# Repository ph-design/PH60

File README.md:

English Version | [中文版](README-zh_CN.md)

**[GitHub Repo](https://github.com/ph-design/PH60) | [Wiki](https://wiki.phdesign.cc/PH60/rev3_multi/) | [Discord](https://discord.gg/8UfQXcefPH) | [Taobao Store](https://shop268559013.taobao.com) | [QQ Group](https://qm.qq.com/q/OY0mIxSRs4) | [Customizer](https://custom.phdesign.cc)**

---

# PH60 Rev.3

**PH60 Rev.3** is a 60% tri-mode mechanical keyboard kit with an FDM 3D-printable case and the PH60 Rev.3 Multi PCB. This revision switches to the NRF52840 MCU with Bluetooth 5.3 and Nordic 2.4 GHz proprietary protocol (TBD), runs [ZMKs](https://github.com/ph-design/zmks) firmware (our fork of ZMK), and redesigns the case for wireless use and multi-layout compatibility.

## Features

### PCB

+ [Nordic NRF52840](https://www.nordicsemi.com/products/nrf52840) MCU, Bluetooth 5.3 + 2.4 GHz (TBD).
+ [ZMKs](https://github.com/ph-design/zmks) firmware with [ZMKs Studio](https://zmks.phdesign.cc/) for real-time keymap editing.
+ Multi-layout support — ANSI / ISO / WK / WKL / HHKB, plus split spacebar: 6.25u → 2.75u + 1u + 2.5u, 7u → 3u + 1u + 3u.
+ Battery powered, built-in battery connector.

> **Note on ANSI/ISO variants:** Rev.3 currently only ships the **Multi** layout PCB. The ANSI PCB in this repo is an early prototype with a fundamentally different design approach — there is no standalone ISO version. We may develop dedicated ANSI/ISO variants based on ZMKs in the future.

### Case

+ Designed for FDM 3D printing — printable on any printer with a bed ≥ 256 × 256 mm, no supports required.
+ Magnetic quick-release latches — tool-free disassembly.
+ O-ring gasket plate mount — firm, crisp feel without foam.
+ Modular battery tray and magnet drawers, fits up to 100 × 50 × 5 mm LiPo and 10 × 5 × 5 mm magnets.
+ Locking holder for wireless receivers, compatible with most commercial 2.4 GHz receiver housings.
+ Multiple outer case variants: Standard, WKL, HHKB (6u/7u), and split backspace options.

### Plates

+ Plates available for ANSI, ISO, WK, HHKB (6u/7u), LS64, EC60, and split-key variants.
+ More layouts added over time.

## What's new compared to Rev.2

| | Rev.2 | Rev.3 |
| --- | --- | --- |
| **MCU** | RP2040 | NRF52840 |
| **Connectivity** | USB only | USB + Bluetooth 5.3 + 2.4 GHz (TBD) |
| **Firmware** | QMK + VIA | ZMKs + ZMKs Studio |
| **Power** | USB powered | Battery powered |
| **Split spacebar** | Not supported | 6.25u & 7u split |
| **Case** | 3-piece modular | Magnetic quick-release, O-ring gasket |

## Customizer

Configure your PH60 Rev.3 with live 3D preview at [custom.phdesign.cc](https://custom.phdesign.cc).

---

## Project Structure

```
PH60 Rev.3
├── Assets/                         # Preview images
├── Case_Model_Rev3/                # Case 3D model files (STEP)
├── LICENSE
├── PCB_Model_Rev3/                 # PCB 3D model files
├── PCB_Rev3/
│   ├── ANSI/                       # ANSI variant (early prototype)
│   └── Multi/                      # Multi-layout variant (primary)
├── Plates_Rev3/                    # Plate files (STEP)
├── Production/
│   ├── PH60-Rev3-ANSI/             # ANSI production files
│   └── PH60-Rev3-Multi/            # Multi production files
├── README.md
└── README-zh_CN.md
```

## Printing Guide

The case prints well with default FDM settings. Recommended parameters for best results:

| Setting | Recommended | Notes |
| --- | --- | --- |
| Filament | PLA or PETG | High-temp materials increase warp risk |
| Layer height | 0.2 mm | Model designed around 0.2 mm |
| Wall count | 2 walls | — |
| Infill pattern | Gyroid | — |
| Infill density | 15% | — |
| Wall generator | Arachne | Improves print speed |
| Accurate outer wall | Enabled | Reduces visible layer lines |
| Support | Off | Designed for supportless printing |

Make sure the bed is leveled and clean before printing. Use adhesive on long parts like the top cover to prevent warping. Sand and clean prints for a better finish.

## Assembly

### Bill of Materials

| Item | Qty | Notes |
| --- | --- | --- |
| 3D printed case parts | 1 set | PLA or PETG recommended |
| PH60 Rev.3 Multi PCB | 1 | Pre-soldered SMD components |
| MX-compatible switches | 61+ | Varies by layout |
| Keycaps | 1 set | Compatible with 60% layout |
| LiPo battery (optional) | 1 | Recommended: 100 × 50 × 5 mm, Molex 1.25 mm connector |
| Magnets | 8 | Recommended: 10 × 5 × 3 mm, N52 |
| Silicone O-rings | 8 | OD 9 mm, cord 1.5 mm |
| Silicone anti-slip pads | 4 | Recommended: 20 × 10 × 2 mm |

For detailed assembly steps, refer to the [Wiki](https://wiki.phdesign.cc/PH60/rev3_multi/).

## Firmware

### Getting Firmware

- **GitHub Actions**: Download from the [ZMKs config repository](https://github.com/ph-design/ph_lite-zmk-config) Actions artifacts.
- **QQ Group**: Join [512933670](https://qm.qq.com/q/OY0mIxSRs4) for firmware files in group shared folder.

### Flashing Firmware

1. **Enter bootloader**: Press `FN + B + R`, or remove the spacebar keycap and double-tap the `BOOT` pads with tweezers.
2. **Flash**: The keyboard appears as a USB storage device. Copy the `.uf2` file to it — the keyboard reboots automatically.

### Keymap Customization

Visit [ZMKs Studio](https://zmks.phdesign.cc/) for real-time keymap editing.

## FAQ

**Q: Which 3D printers can print the Rev.3 case?**
A: Any FDM printer with a bed ≥ 256 × 256 mm that can print PLA or PETG.

**Q: Which layouts does the Rev.3 case support?**
A: ANSI, ISO, HHKB, WK, WKL, LS64, and EC60 (NIZ electrostatic capacitive). Plate designs are continuously updated.

**Q: Why is there no dedicated ANSI or ISO PCB?**
A: The early ANSI prototype has a fundamentally different design from the Multi PCB. We focused on Multi to support all layouts with a single board. Dedicated variants may come later based on ZMKs.

**Q: What battery and magnet sizes are supported?**
A: Up to 100 × 50 × 5 mm LiPo battery. Magnets: 10 × 5 × 3 mm (N52 recommended). The battery tray and magnet drawers can be modified for other sizes.

## Getting Help

- GitHub Issues: [ph-design/PH60](https://github.com/ph-design/PH60/issues)
- Discord: [discord.gg/phdesign](https://discord.gg/8UfQXcefPH)
- QQ Group: [512933670](https://qm.qq.com/q/OY0mIxSRs4)
- Wiki: [wiki.phdesign.cc](https://wiki.phdesign.cc/)

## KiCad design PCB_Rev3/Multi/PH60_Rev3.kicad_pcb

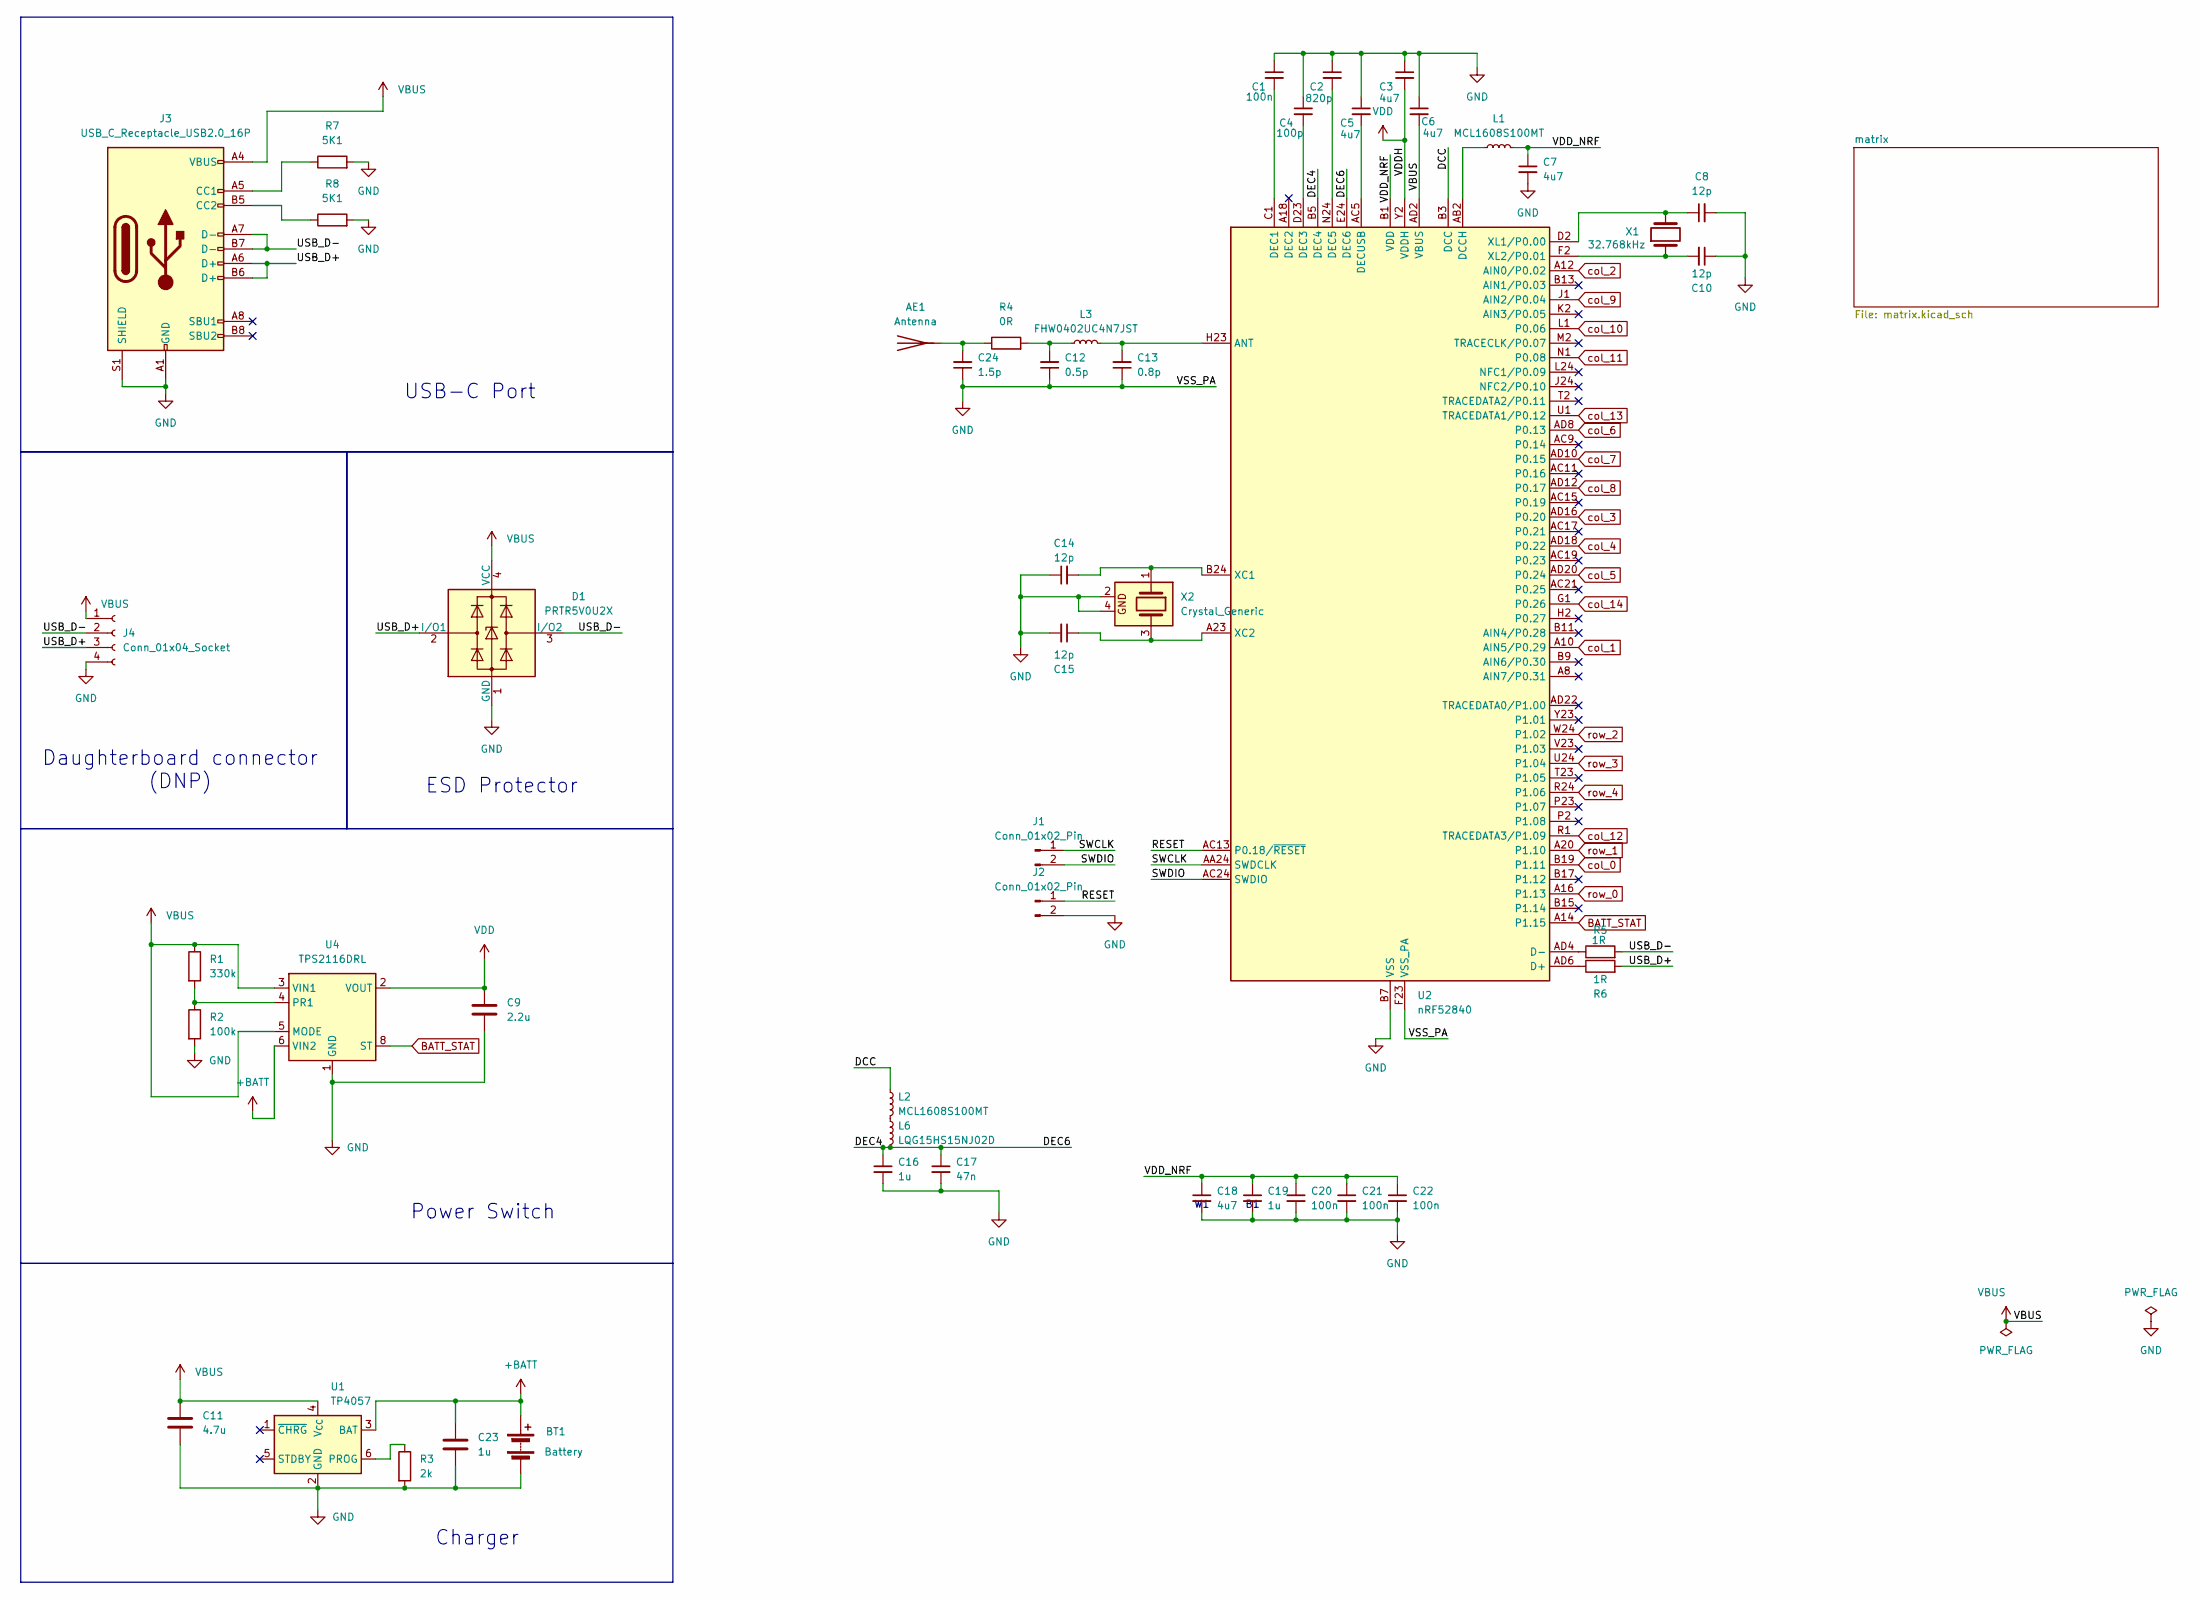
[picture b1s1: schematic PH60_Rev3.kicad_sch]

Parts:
AE1: Antenna; nrf52_ant_1.6mm
BT1: Battery; Molex_PicoBlade_53261-0271_1x02-1MP_P1.25mm_Horizontal
C1, C20, C21, C22: 100n; C_0402_1005Metric
C2: 820p; C_0402_1005Metric
C3, C5, C6, C7, C18: 4u7; C_0402_1005Metric
C4: 100p; C_0402_1005Metric
C8, C10, C14, C15: 12p; C_0402_1005Metric
C9: 2.2u; C_0402_1005Metric
C11: 4.7u; C_0402_1005Metric
C12: 0.5p; C_0402_1005Metric
C13: 0.8p; C_0402_1005Metric
C16, C19, C23: 1u; C_0402_1005Metric
C17: 47n; C_0603_1608Metric
C24: 1.5p; C_0402_1005Metric
D1: PRTR5V0U2X; SOT-143
J1, J2: Conn_01x02_Pin; PinHeader_1x02_P2.00mm_Vertical
J3: USB_C_Receptacle_USB2.0_16P; USB-C_16P_HandSolder
J4: Conn_01x04_Socket; Molex_Pico-EZmate_78171-0004_1x04-1MP_P1.20mm_Vertical
L1, L2: MCL1608S100MT; L_0603_1608Metric
L3: FHW0402UC4N7JST; L_0402_1005Metric
L6: LQG15HS15NJ02D; L_0402_1005Metric
R1: 330k; R_0402_1005Metric
R2: 100k; R_0402_1005Metric
R3: 2k; R_0402_1005Metric
R4: 0R; C_0402_1005Metric
R5, R6: 1R; C_0402_1005Metric
R7, R8: 5K1; R_0402_1005Metric
U1: TP4057; TSOT-23-6
U2: nRF52840; Nordic_AQFN-73-1EP_7x7mm_P0.5mm_2_Layer_Board
U4: TPS2116DRL; SOT-583-8
X1: 32.768kHz; Crystal_SMD_3215-2Pin_3.2x1.5mm
X2: Crystal_Generic; Crystal_SMD_2016-4Pin_2.0x1.6mm

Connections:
+BATT: BT1.1 (+), C23.1, U1.3 (BAT), U4.6 (VIN2)
/DCC: L2.1, U2.B3 (DCC)
/DEC4: C16.1, C17.1, L6.2, U2.B5 (DEC4), U2.E24 (DEC6)
/RESET: J2.1, U2.AC13 (P0.18/~RESET)
/SWCLK: J1.1, U2.AA24 (SWDCLK)
/SWDIO: J1.2, U2.AC24 (SWDIO)
/USB_D+: D1.2 (I/O1), J3.A6 (D+), J3.B6 (D+), J4.3, R6.2
/USB_D-: D1.3 (I/O2), J3.A7 (D-), J3.B7 (D-), J4.2, R5.2
/VDD_NRF: C7.1, C18.1, C19.1, C20.1, C21.1, C22.1, L1.2, U2.A22 (VDD), U2.AD14 (VDD), U2.AD23 (VDD), U2.B1 (VDD), U2.W1 (VDD)
BATT_STAT: U2.A14 (P1.15), U4.8 (ST)
GND: BT1.2 (-), C1.1, C2.1, C3.1, C4.1, C5.1, C6.1, C7.2, C8.2, C9.2, C10.1, C11.2, C12.1, C13.1, C14.1, C15.2, C16.2, C17.2, C18.2, C19.2, C20.2, C21.2, C22.2, C23.2, C24.1, D1.1 (GND), J2.2, J3.A1 (GND), J3.A12 (GND), J3.B1 (GND), J3.B12 (GND), J3.S1 (SHIELD), J4.4, R2.2, R3.2, R7.2, R8.2, U1.2 (GND), U2.B7 (VSS), U2.EP (VSS), U2.F23 (VSS_PA), U4.1 (GND), X2.2, X2.4
unnamed: AE1.1 (A), C24.2, R4.1
unnamed: C12.2, L3.1, R4.2
unnamed: J3.A5 (CC1), R7.1
unnamed: J3.B5 (CC2), R8.1
unnamed: L2.2, L6.1
unnamed: R3.1, U1.6 (PROG)
unnamed: C13.2, L3.2, U2.H23 (ANT)
unnamed: R6.1, U2.AD6 (D+)
unnamed: R5.1, U2.AD4 (D-)
unnamed: L1.1, U2.AB2 (DCCH)
unnamed: C1.2, U2.C1 (DEC1)
unnamed: C4.2, U2.D23 (DEC3)
unnamed: C2.2, U2.N24 (DEC5)
unnamed: C5.2, U2.AC5 (DECUSB)
unnamed: C14.2, U2.B24 (XC1), X2.1
unnamed: C15.1, U2.A23 (XC2), X2.3
unnamed: C8.1, U2.D2 (XL1/P0.00), X1.2
unnamed: C10.2, U2.F2 (XL2/P0.01), X1.1
unnamed: R1.2, R2.1, U4.4 (PR1)
VBUS: C6.2, C11.1, D1.4 (VCC), J3.A4 (VBUS), J3.A9 (VBUS), J3.B4 (VBUS), J3.B9 (VBUS), J4.1, R1.1, U1.4 (V_{CC}), U2.AD2 (VBUS), U4.3 (VIN1), U4.5 (MODE)
VDD: C3.2, C9.1, U2.Y2 (VDDH), U4.2 (VOUT), U4.7 (VOUT)
col_0: U2.B19 (P1.11); also elsewhere on the board
col_1: U2.A10 (AIN5/P0.29); also elsewhere on the board
col_2: U2.A12 (AIN0/P0.02); also elsewhere on the board
col_3: U2.AD16 (P0.20); also elsewhere on the board
col_4: U2.AD18 (P0.22); also elsewhere on the board
col_5: U2.AD20 (P0.24); also elsewhere on the board
col_6: U2.AD8 (P0.13); also elsewhere on the board
col_7: U2.AD10 (P0.15); also elsewhere on the board
col_8: U2.AD12 (P0.17); also elsewhere on the board
col_9: U2.J1 (AIN2/P0.04); also elsewhere on the board
col_10: U2.L1 (P0.06); also elsewhere on the board
col_11: U2.N1 (P0.08); also elsewhere on the board
col_12: U2.R1 (TRACEDATA3/P1.09); also elsewhere on the board
col_13: U2.U1 (TRACEDATA1/P0.12); also elsewhere on the board
col_14: U2.G1 (P0.26); also elsewhere on the board
row_0: U2.A16 (P1.13); also elsewhere on the board
row_1: U2.A20 (P1.10); also elsewhere on the board
row_2: U2.W24 (P1.02); also elsewhere on the board
row_3: U2.U24 (P1.04); also elsewhere on the board
row_4: U2.R24 (P1.06); also elsewhere on the board

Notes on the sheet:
ESD Protector
USB-C Port
Charger
Daughterboard connector (DNP)
Power Switch

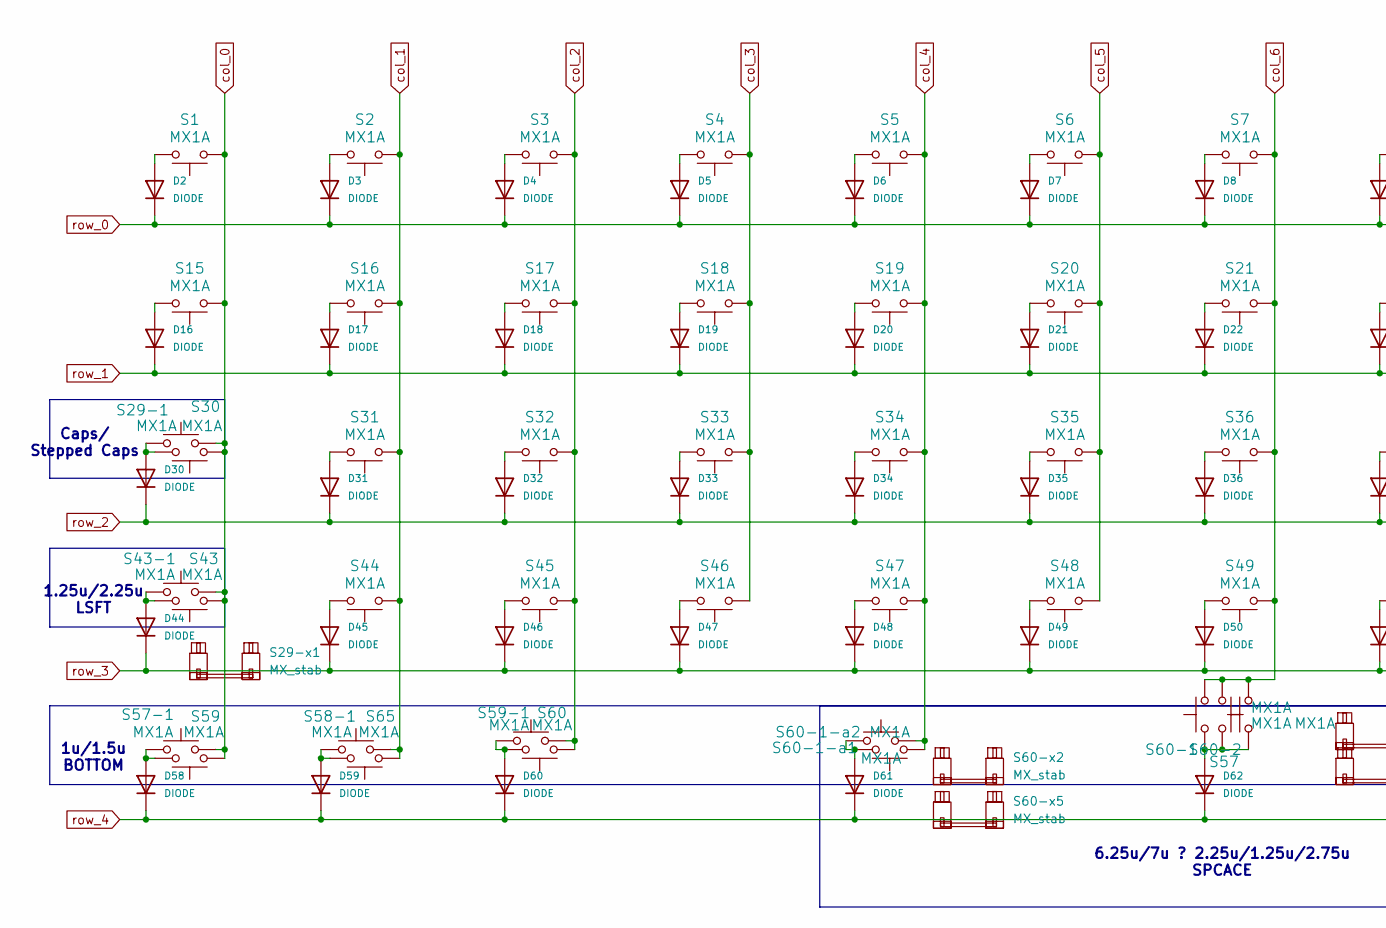
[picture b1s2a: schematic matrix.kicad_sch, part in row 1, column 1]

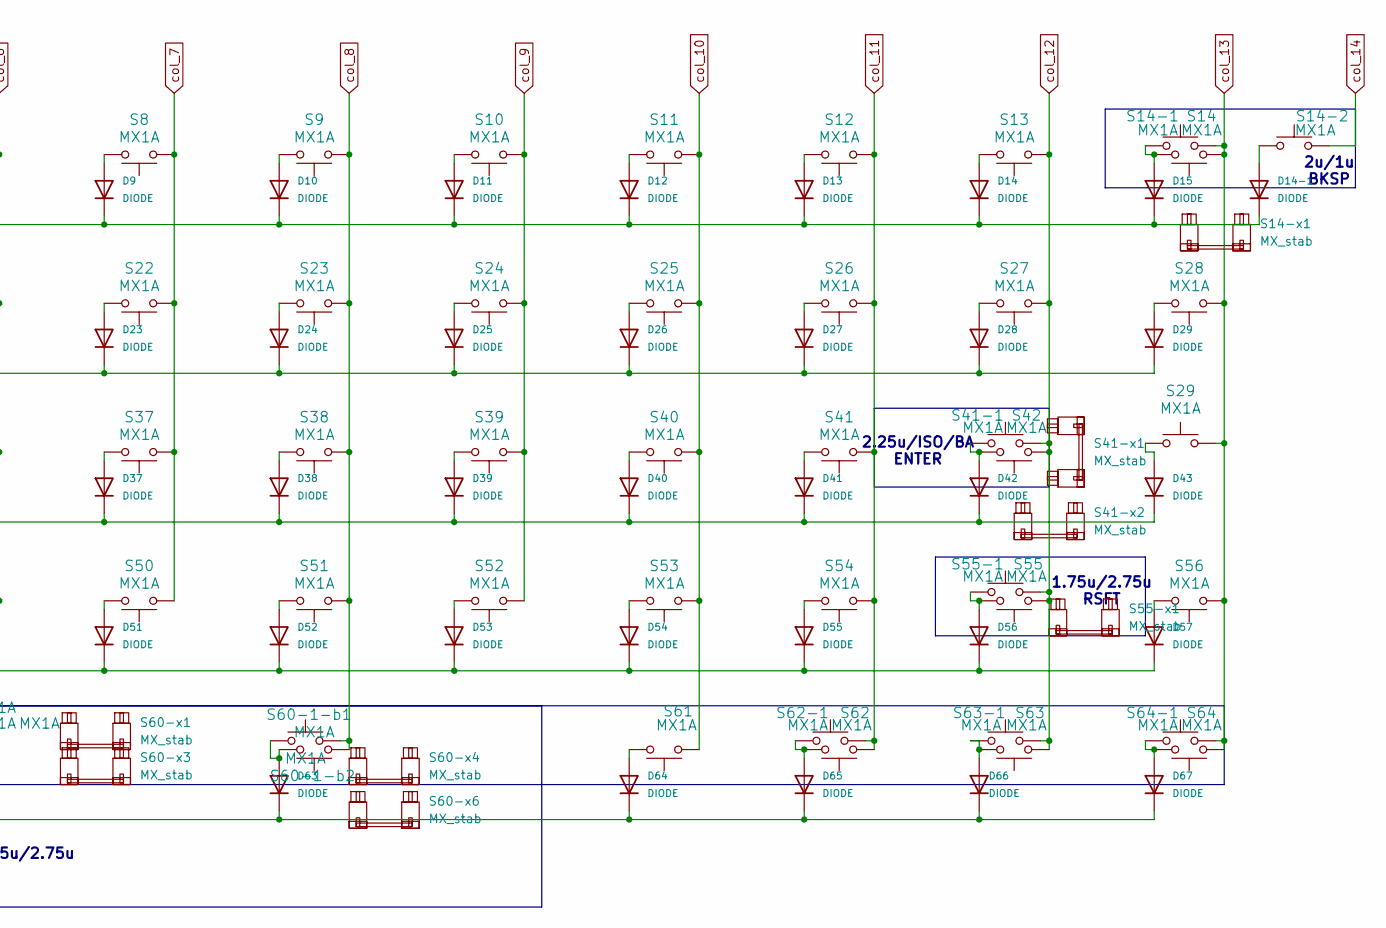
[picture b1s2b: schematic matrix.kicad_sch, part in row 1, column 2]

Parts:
D2, D3, D4, D5, D6, D7, D8, D9, D10, D11, D12, D13, D14, D14-1, D15, D16, D17, D18, D19, D20, D21, D22, D23, D24, D25, D26, D27, D28, D29, D30, D31, D32, D33, D34, D35, D36, D37, D38, D39, D40, D41, D42, D43, D44, D45, D46, D47, D48, D49, D50, D51, D52, D53, D54, D55, D56, D57, D58, D59, D60, D61, D62, D63, D64, D65, D66, D67: DIODE; D_SOD-123
S1, S2, S3, S4, S5, S6, S7, S8, S9, S10, S11, S12, S13, S14-1, S14-2, S16, S17, S18, S19, S20, S21, S22, S23, S24, S25, S26, S27, S29, S31, S32, S33, S34, S35, S36, S37, S38, S39, S40, S41, S44, S45, S46, S47, S48, S49, S50, S51, S52, S53, S54, S56, S58-1, S63-1: MX1A; SW_Hotswap_Kailh_MX_Plated_1.00u
S14: MX1A; SW_Hotswap_Kailh_MX_Plated_2.00u
S14-x1, S29-x1, S41-x1, S41-x2, S55-x1, S60-x2, S60-x4, S60-x5, S60-x6: MX_stab; Stabilizer_Cherry_MX_2.00u
S15, S57-1, S59-1, S62-1, S64-1: MX1A; SW_Hotswap_Kailh_MX_Plated_1.50u
S28: MX1A; SW_Hotswap_Kailh_MX_Plated_1.50u_90deg
S29-1, S43, S57, S59, S60, S61, S62, S63, S64, S65: MX1A; SW_Hotswap_Kailh_MX_Plated_1.25u
S30, S55: MX1A; SW_Hotswap_Kailh_MX_Plated_1.75u
S41-1: MX1A; SW_Hotswap_Kailh_MX_Plated_ISOEnter_90deg
S42: MX1A; SW_Hotswap_Kailh_MX_Plated_2.25u_90deg
S43-1, S60-1-a1: MX1A; SW_Hotswap_Kailh_MX_Plated_2.25u
S55-1, S60-1-b1: MX1A; SW_Hotswap_Kailh_MX_Plated_2.75u
S60-1: MX1A; SW_Hotswap_Kailh_MX_Plated_7.00u
S60-1-a2, S60-1-b2: MX1A; SW_Hotswap_Kailh_MX_Plated_3.00u
S60-2: MX1A; SW_Hotswap_Kailh_MX_Plated_6.25u
S60-x1: MX_stab; Stabilizer_Cherry_MX_6.25u
S60-x3: MX_stab; Stabilizer_Cherry_MX_7.00u

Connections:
unnamed: D2.2 (A), S1.1
unnamed: D3.2 (A), S2.1
unnamed: D4.2 (A), S3.1
unnamed: D5.2 (A), S4.1
unnamed: D6.2 (A), S5.1
unnamed: D7.2 (A), S6.1
unnamed: D8.2 (A), S7.1
unnamed: D9.2 (A), S8.1
unnamed: D10.2 (A), S9.1
unnamed: D11.2 (A), S10.1
unnamed: D12.2 (A), S11.1
unnamed: D13.2 (A), S12.1
unnamed: D14-1.2 (A), S14-2.2
unnamed: D14.2 (A), S13.1
unnamed: D15.2 (A), S14.1, S14-1.2
unnamed: D16.2 (A), S15.1
unnamed: D17.2 (A), S16.1
unnamed: D18.2 (A), S17.1
unnamed: D19.2 (A), S18.1
unnamed: D20.2 (A), S19.1
unnamed: D21.2 (A), S20.1
unnamed: D22.2 (A), S21.1
unnamed: D23.2 (A), S22.1
unnamed: D24.2 (A), S23.1
unnamed: D25.2 (A), S24.1
unnamed: D26.2 (A), S25.1
unnamed: D27.2 (A), S26.1
unnamed: D28.2 (A), S27.1
unnamed: D29.2 (A), S28.1
unnamed: D30.2 (A), S29-1.2, S30.1
unnamed: D31.2 (A), S31.1
unnamed: D32.2 (A), S32.1
unnamed: D33.2 (A), S33.1
unnamed: D34.2 (A), S34.1
unnamed: D35.2 (A), S35.1
unnamed: D36.2 (A), S36.1
unnamed: D37.2 (A), S37.1
unnamed: D38.2 (A), S38.1
unnamed: D39.2 (A), S39.1
unnamed: D40.2 (A), S40.1
unnamed: D41.2 (A), S41.1
unnamed: D42.2 (A), S41-1.2, S42.1
unnamed: D43.2 (A), S29.2
unnamed: D44.2 (A), S43.1, S43-1.2
unnamed: D45.2 (A), S44.1
unnamed: D46.2 (A), S45.1
unnamed: D47.2 (A), S46.1
unnamed: D48.2 (A), S47.1
unnamed: D49.2 (A), S48.1
unnamed: D50.2 (A), S49.1
unnamed: D51.2 (A), S50.1
unnamed: D52.2 (A), S51.1
unnamed: D53.2 (A), S52.1
unnamed: D54.2 (A), S53.1
unnamed: D55.2 (A), S54.1
unnamed: D56.2 (A), S55.1, S55-1.2
unnamed: D57.2 (A), S56.1
unnamed: D58.2 (A), S57-1.1, S59.2
unnamed: D59.2 (A), S58-1.2, S65.1
unnamed: D60.2 (A), S59-1.2, S60.1
unnamed: D61.2 (A), S60-1-a1.1, S60-1-a2.2
unnamed: D62.2 (A), S57.1, S60-1.2, S60-2.2
unnamed: D63.2 (A), S60-1-b1.1, S60-1-b2.2
unnamed: D64.2 (A), S61.1
unnamed: D65.2 (A), S62.1, S62-1.2
unnamed: D66.2 (A), S63.1, S63-1.2
unnamed: D67.2 (A), S64.1, S64-1.2
col_0: S1.2, S15.2, S29-1.1, S30.2, S43.2, S43-1.1, S57-1.2, S59.1; also elsewhere on the board
col_1: S2.2, S16.2, S31.2, S44.2, S58-1.1, S65.2; also elsewhere on the board
col_2: S3.2, S17.2, S32.2, S45.2, S59-1.1, S60.2; also elsewhere on the board
col_3: S4.2, S18.2, S33.2, S46.2; also elsewhere on the board
col_4: S5.2, S19.2, S34.2, S47.2, S60-1-a1.2, S60-1-a2.1; also elsewhere on the board
col_5: S6.2, S20.2, S35.2, S48.2; also elsewhere on the board
col_6: S7.2, S21.2, S36.2, S49.2, S57.2, S60-1.1, S60-2.1; also elsewhere on the board
col_7: S8.2, S22.2, S37.2, S50.2; also elsewhere on the board
col_8: S9.2, S23.2, S38.2, S51.2, S60-1-b1.2, S60-1-b2.1; also elsewhere on the board
col_9: S10.2, S24.2, S39.2, S52.2; also elsewhere on the board
col_10: S11.2, S25.2, S40.2, S53.2, S61.2; also elsewhere on the board
col_11: S12.2, S26.2, S41.2, S54.2, S62.2, S62-1.1; also elsewhere on the board
col_12: S13.2, S27.2, S41-1.1, S42.2, S55.2, S55-1.1, S63.2, S63-1.1; also elsewhere on the board
col_13: S14.2, S14-1.1, S28.2, S29.1, S56.2, S64.2, S64-1.1; also elsewhere on the board
col_14: S14-2.1; also elsewhere on the board
row_0: D2.1 (K), D3.1 (K), D4.1 (K), D5.1 (K), D6.1 (K), D7.1 (K), D8.1 (K), D9.1 (K), D10.1 (K), D11.1 (K), D12.1 (K), D13.1 (K), D14.1 (K), D14-1.1 (K), D15.1 (K); also elsewhere on the board
row_1: D16.1 (K), D17.1 (K), D18.1 (K), D19.1 (K), D20.1 (K), D21.1 (K), D22.1 (K), D23.1 (K), D24.1 (K), D25.1 (K), D26.1 (K), D27.1 (K), D28.1 (K), D29.1 (K); also elsewhere on the board
row_2: D30.1 (K), D31.1 (K), D32.1 (K), D33.1 (K), D34.1 (K), D35.1 (K), D36.1 (K), D37.1 (K), D38.1 (K), D39.1 (K), D40.1 (K), D41.1 (K), D42.1 (K), D43.1 (K); also elsewhere on the board
row_3: D44.1 (K), D45.1 (K), D46.1 (K), D47.1 (K), D48.1 (K), D49.1 (K), D50.1 (K), D51.1 (K), D52.1 (K), D53.1 (K), D54.1 (K), D55.1 (K), D56.1 (K), D57.1 (K); also elsewhere on the board
row_4: D58.1 (K), D59.1 (K), D60.1 (K), D61.1 (K), D62.1 (K), D63.1 (K), D64.1 (K), D65.1 (K), D66.1 (K), D67.1 (K); also elsewhere on the board

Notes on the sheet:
2.25u/ISO/BA ENTER
6.25u/7u ? 2.25u/1.25u/2.75u SPCACE
Caps/ Stepped Caps
2u/1u BKSP
1.75u/2.75u RSFT
1.25u/2.25u LSFT
1u/1.5u BOTTOM

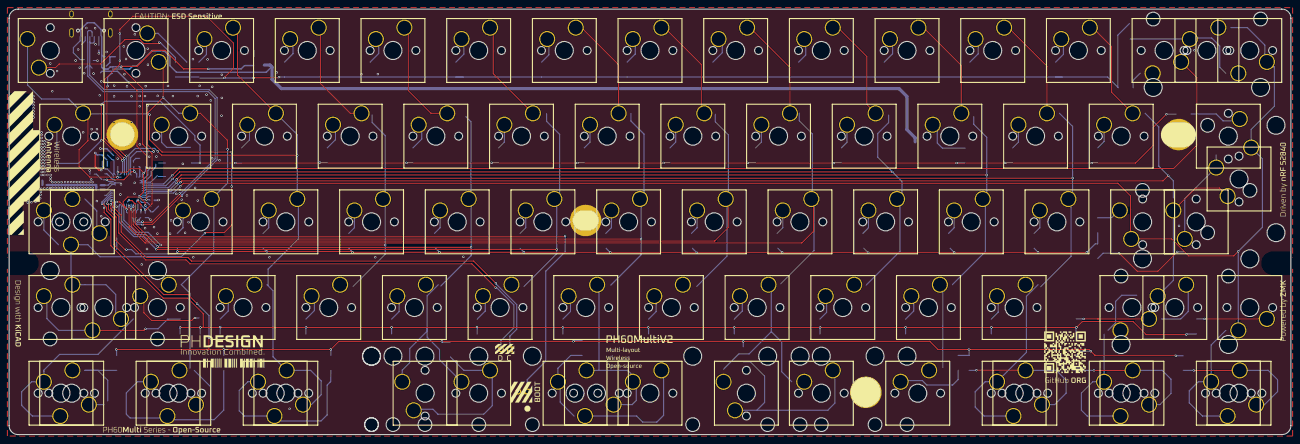
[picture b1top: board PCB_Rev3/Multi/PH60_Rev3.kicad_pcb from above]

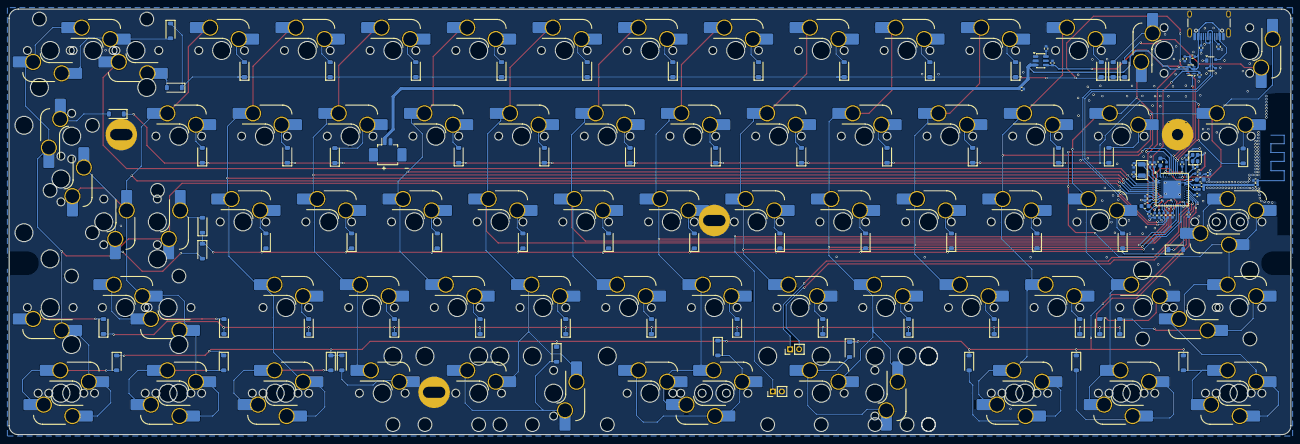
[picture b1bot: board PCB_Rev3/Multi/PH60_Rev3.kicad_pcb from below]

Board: 2 copper layers, 285.0 x 94.6 mm, 213 parts (114 on the bottom side), 119 nets.

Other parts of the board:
HOLE: VAL**; PKRH
HOLE#2, HOLE#6: VAL**; PKRH
HOLE#3, HOLE#5: VAL**; PKRHSL
HOLE#4: VAL**; PKRHC

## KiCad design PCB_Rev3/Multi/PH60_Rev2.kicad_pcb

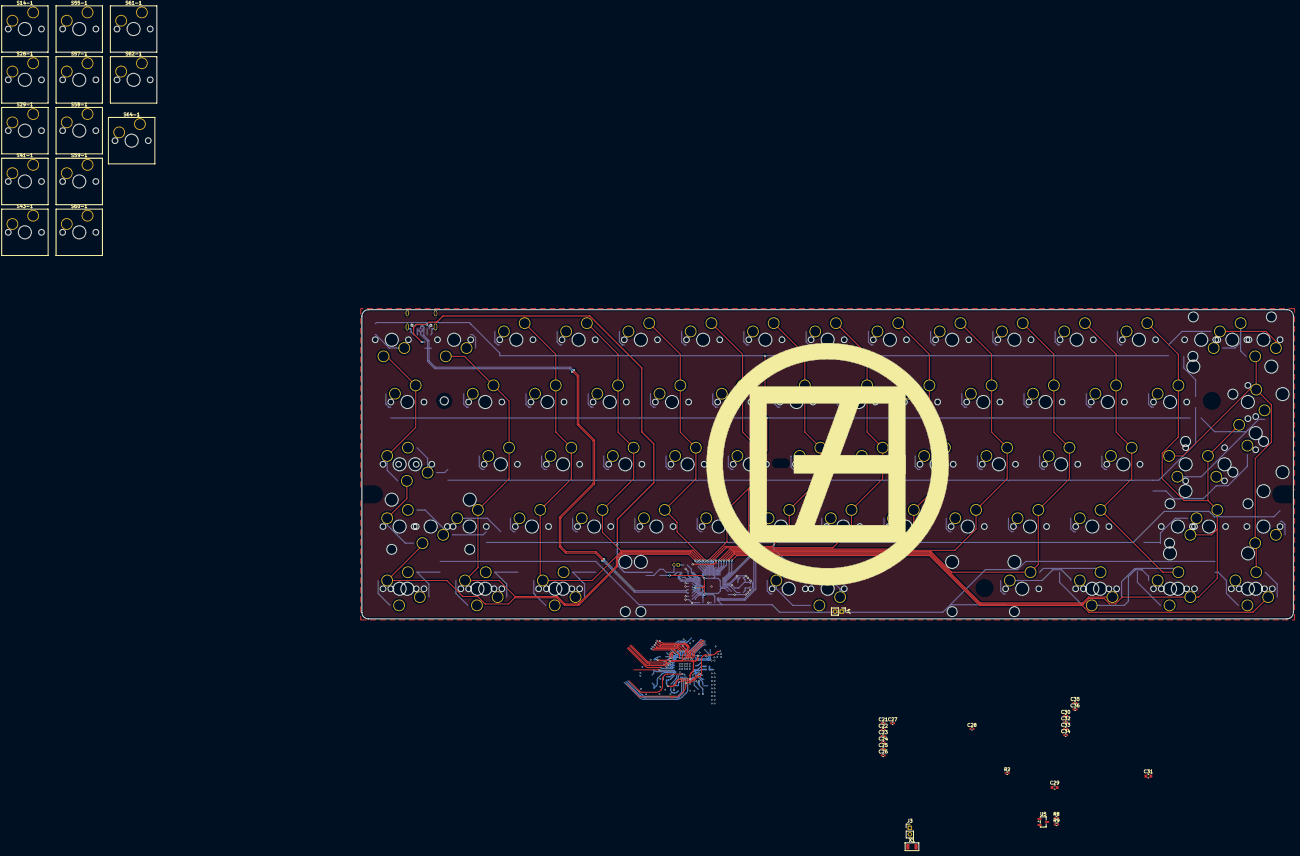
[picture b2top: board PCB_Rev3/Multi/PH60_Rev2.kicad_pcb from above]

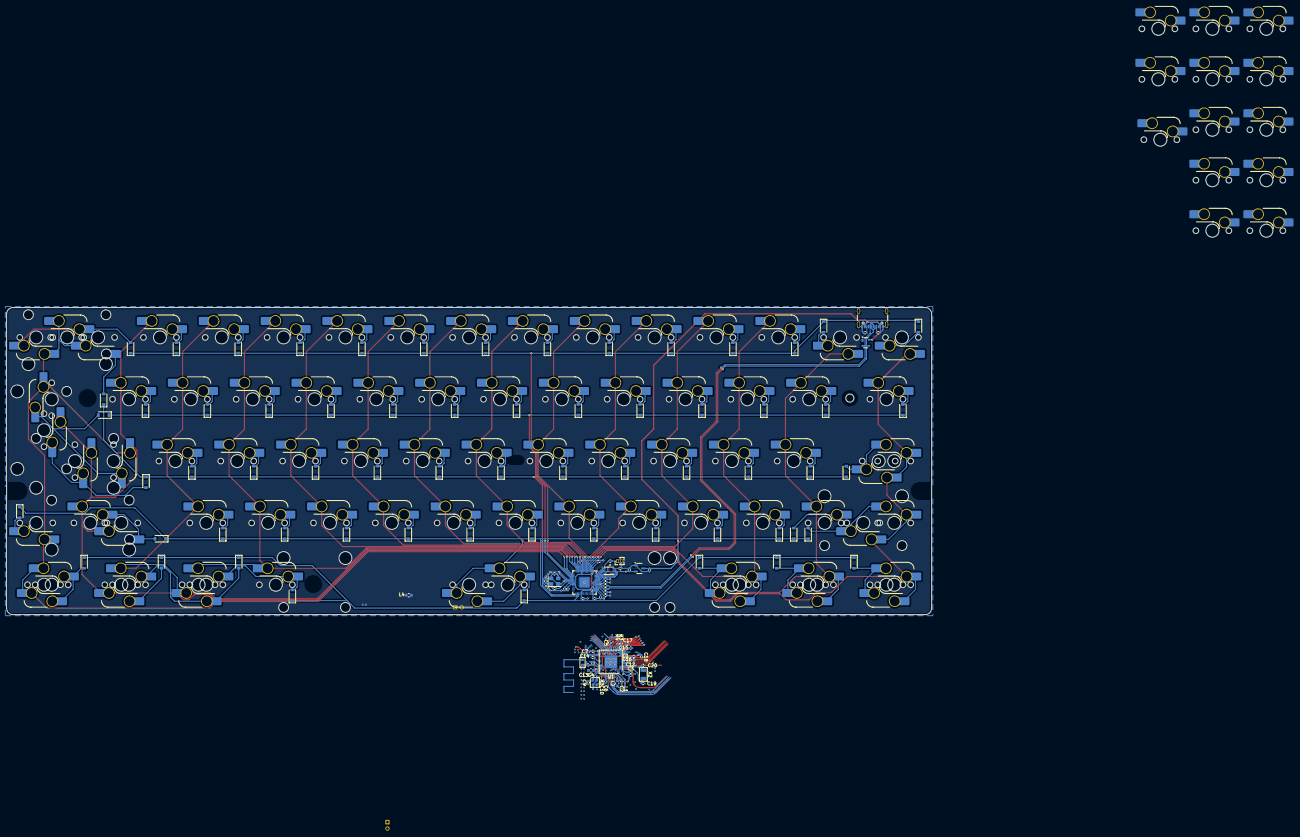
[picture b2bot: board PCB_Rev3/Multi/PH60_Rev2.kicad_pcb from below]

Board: 2 copper layers, 285.0 x 94.6 mm, 243 parts (124 on the bottom side), 115 nets.

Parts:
AE1: Antenna; nrf52_ant_1.6mm
C1, C1#2, C8, C8#2, C9, C9#2, C12, C12#2, C23, C34, C35, C36: 100n; C_0402_1005Metric
C2, C2#2, C14, C14#2: 820p; C_0402_1005Metric
C3, C3#2, C10, C10#2, C17, C18, C19, C24, C25: 12p; C_0402_1005Metric
C4, C13, C13#2: 100p; C_0402_1005Metric
C4#2: 100p; C_0603_1608Metric
C5, C5#2, C6, C6#2, C7, C7#2, C15, C15#2, C16, C16#2, C28, C32: 4u7; C_0402_1005Metric
C11, C11#2, C22: 0.8p; C_0402_1005Metric
C20, C21: 0.5p; C_0402_1005Metric
C26, C27, C30, C33: 1u; C_0402_1005Metric
C29, C31: 47n; C_0603_1608Metric
D1: PRTR5V0U2X; D_SOD-123
D2, D3, D4, D5, D6, D7, D8, D9, D10, D11, D12, D13, D14, D15, D16, D17, D18, D19, D20, D21, D22, D23, D24, D25, D26, D27, D28, D29, D30, D31, D32, D33, D34, D35, D36, D37, D38, D39, D40, D41, D42, D43, D44, D45, D46, D47, D48, D49, D50, D51, D52, D53, D54, D55, D56, D57, D58, D59, D60, D61, D62, D63, D64: DIODE; D_SOD-123
D65: DIODE; SOT-143
HOLE: VAL**; PKRH
HOLE#2, HOLE#6: VAL**; PKRH
HOLE#3, HOLE#5: VAL**; PKRHSL
HOLE#4: VAL**; PKRHC
J1: Conn_01x02; USB_C_Receptacle_GCT_USB4105-xx-A_16P_TopMnt_Horizontal
J2: Conn_01x02_Pin; PinHeader_1x02_P1.27mm_Vertical
J3: Conn_01x02_Pin; PinHeader_1x02_P2.00mm_Vertical
J4: USB_C_Receptacle_USB2.0_16P; PinHeader_1x02_P2.00mm_Vertical
L1: MCL1608S100MT; L_0402_1005Metric
L2: FHW0402UC4N7JST; L_0603_1608Metric
L3: LQG15HS15NJ02D; L_0402_1005Metric
L4: MCL1608S100MT; L_0603_1608Metric
R1, R4: 0R; R_0402_1005Metric
R1#2: 0R; R_0603_1608Metric
R2, R3: 1R; C_0402_1005Metric
R3#2, R5, R6: 1R; R_0402_1005Metric
R4#2: 0R; C_0402_1005Metric
R7: 1k; R_0402_1005Metric
R8, R9: 5K1; R_0402_1005Metric
S1, S2, S3, S4, S5, S6, S7, S8, S9, S10, S11, S12, S13, S14-1, S14-2, S16, S17, S18, S19, S20, S21, S22, S23, S24, S25, S26, S27, S30, S31, S32, S33, S34, S35, S36, S37, S38, S39, S40, S41, S42, S44, S45, S46, S47, S48, S49, S50, S51, S52, S53, S54, S56, S58-1, S58-2, S62-1, S62-2: MX1A; SW_Hotswap_Kailh_MX_Plated_1.00u
S14: MX1A; SW_Hotswap_Kailh_MX_Plated_2.00u
S15, S57-1, S57-2, S59-1, S59-2, S61-1, S61-2, S64-1, S64-2: MX1A; SW_Hotswap_Kailh_MX_Plated_1.50u
S28: MX1A; SW_Hotswap_Kailh_MX_Plated_ISOEnter_90deg
S28-1, S28-2: MX1A; SW_Hotswap_Kailh_MX_Plated_1.50u_90deg
S29, S55: MX1A; SW_Hotswap_Kailh_MX_Plated_1.75u
S29-1, S29-2, S43, S57, S58, S59, S61, S62, S63, S64: MX1A; SW_Hotswap_Kailh_MX_Plated_1.25u
S41-1, S41-2: MX1A; SW_Hotswap_Kailh_MX_Plated_2.25u_90deg
S43-1, S43-2: MX1A; SW_Hotswap_Kailh_MX_Plated_2.25u
S55-1, S55-2: MX1A; SW_Hotswap_Kailh_MX_Plated_2.75u
S60: MX1A; SW_Hotswap_Kailh_MX_Plated_6.25u
S60-1, S60-2: MX1A; SW_Hotswap_Kailh_MX_Plated_7.00u
U1: nRF52840; Nordic_AQFN-73-1EP_7x7mm_P0.5mm_2_Layer_Board
U2: RP2040; Winbond_USON-8-1EP_3x2mm_P0.5mm_EP0.2x1.6mm
U3: W25Q128JVS; QFN-56-1EP_7x7mm_P0.4mm_EP3.2x3.2mm
U4, U5: XC6206PxxxMR; SOT-23-3
X1: 32.768kHz; Crystal_SMD_3215-2Pin_3.2x1.5mm
X2: Crystal_Generic; Crystal_SMD_3215-2Pin_3.2x1.5mm
X3: Crystal_Generic; Crystal_SMD_2016-4Pin_2.0x1.6mm
Y1: Crystal_GND24; Crystal_SMD_3225-4Pin_3.2x2.5mm

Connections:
+1V1: C8.1, C8#2.1, C9.1, C9#2.1, C20.1
+3V3: C10.1, C10#2.1, C11.1, C11#2.1, C12.1, C12#2.1, C13.1, C13#2.1, C14.1, C14#2.1, C15.1, C15#2.1, C16.1, C16#2.1, C19.1, C23.1, C29.1, U2.1 (IOVDD), U3.8 (VCC), U4.2 (VO), U5.2 (VO)
/DCC: L3.1, U1.B3 (DCC)
/DEC4: C30.1, C31.1, L4.2, U1.B5 (DEC4), U1.E24 (DEC6)
/QSPI_SS: R4.2, R4#2.2, U3.1 (~CS)
/RESET: J3.1, U1.AC13 (P0.18/~RESET)
/SWCLK: J2.1, U1.AA24 (SWDCLK)
/SWDIO: J2.2, U1.AC24 (SWDIO)
/USB_D+: D1.2 (I/O1), R2.1, R6.2
/USB_D-: R3.1, R3#2.1, R5.2
/XIN: C26.1, Y1.3
/~USB_BOOT: R4.1, R4#2.1
GND: C1.1, C1#2.1, C2.1, C2#2.1, C3.1, C3#2.1, C4.1, C4#2.1, C5.1, C5#2.1, C6.1, C6#2.1, C7.2, C7#2.2, C8.2, C8#2.2, C9.2, C9#2.2, C10.2, C10#2.2, C11.2, C11#2.2, C12.2, C12#2.2, C13.2, C13#2.2, C14.2, C14#2.2, C15.2, C15#2.2, C16.2, C16#2.2, C17.2, C18.1, C19.2, C20.2, C21.1, C22.1, C23.2, C24.1, C25.2, C26.2, C27.2, C28.2, C29.2, C30.2, C31.2, C32.2, C33.2, C34.2, C35.2, C36.2, D1.1 (GND), J3.2, R8.2, R9.2, U1.B7 (VSS), U1.EP (VSS), U1.F23 (VSS_PA), U3.4 (GND), U4.1 (GND), U5.1 (GND), X2.2, X3.2, X3.4, Y1.2, Y1.4
unnamed: AE1.1 (A), R1.1, R1#2.1
unnamed: C21.2, L2.1, R1.2, R1#2.2
unnamed: C27.1, R7.1, Y1.1
unnamed: D2.2 (A), S1.1
unnamed: D3.2 (A), S2.1
unnamed: D4.2 (A), S3.1
unnamed: D5.2 (A), S4.1
unnamed: D6.2 (A), S5.1
unnamed: D7.2 (A), S6.1
unnamed: D8.2 (A), S7.1
unnamed: D9.2 (A), S8.1
unnamed: D10.2 (A), S9.1
unnamed: D11.2 (A), S10.1
unnamed: D12.2 (A), S11.1
unnamed: D13.2 (A), S12.1
unnamed: D14.2 (A), S13.1, S14-2.1
unnamed: D15.2 (A), S14.1, S14-1.1
unnamed: D16.2 (A), S15.1
unnamed: D17.2 (A), S16.1
unnamed: D18.2 (A), S17.1
unnamed: D19.2 (A), S18.1
unnamed: D20.2 (A), S19.1
unnamed: D21.2 (A), S20.1
unnamed: D22.2 (A), S21.1
unnamed: D23.2 (A), S22.1
unnamed: D24.2 (A), S23.1
unnamed: D25.2 (A), S24.1
unnamed: D26.2 (A), S25.1
unnamed: D27.2 (A), S26.1
unnamed: D28.2 (A), S27.1, S28-2.2
unnamed: D29.2 (A), S28.1, S28-1.2, S29-2.2
unnamed: D30.2 (A), S29.1, S29-1.2
unnamed: D31.2 (A), S30.1
unnamed: D32.2 (A), S31.1
unnamed: D33.2 (A), S32.1
unnamed: D34.2 (A), S33.1
unnamed: D35.2 (A), S34.1
unnamed: D36.2 (A), S35.1
unnamed: D37.2 (A), S36.1
unnamed: D38.2 (A), S37.1
unnamed: D39.2 (A), S38.1
unnamed: D40.2 (A), S39.1
unnamed: D41.2 (A), S40.1, S41-2.1
unnamed: D42.2 (A), S41.1, S41-1.1
unnamed: D43.2 (A), S42.2, S43-2.1
unnamed: D44.2 (A), S43.2, S43-1.1
unnamed: D45.2 (A), S44.1
unnamed: D46.2 (A), S45.1
unnamed: D47.2 (A), S46.1
unnamed: D48.2 (A), S47.1
unnamed: D49.2 (A), S48.1
unnamed: D50.2 (A), S49.1
unnamed: D51.2 (A), S50.1
unnamed: D52.2 (A), S51.1
unnamed: D53.2 (A), S52.1
unnamed: D54.2 (A), S53.1
unnamed: D55.2 (A), S54.1, S55-2.1
unnamed: D56.2 (A), S55.2, S55-1.1
unnamed: D57.2 (A), S56.1, S57-2.1
unnamed: D58.2 (A), S57.2, S57-1.1, S58-2.1
unnamed: D59.2 (A), S58.2, S58-1.1, S59-2.1
unnamed: D60.2 (A), S59.2, S59-1.1, S60-2.2
unnamed: D61.2 (A), S60.1, S60-1.2, S61-2.1
unnamed: D62.2 (A), S61.1, S61-1.1, S62-2.1
unnamed: D63.2 (A), S62.2, S62-1.1
unnamed: D64.2 (A), S63.2, S64-2.1
unnamed: D65.2 (A), S64.2, S64-1.1
unnamed: L3.2, L4.1
unnamed: C22.2, L2.2, U1.H23 (ANT)
unnamed: R6.1, U1.AD6 (D+)
unnamed: R5.1, U1.AD4 (D-)
unnamed: L1.1, U1.AB2 (DCCH)
unnamed: C1.2, C1#2.2, U1.C1 (DEC1)
unnamed: C4.2, C4#2.2, U1.D23 (DEC3)
unnamed: C2.2, C2#2.2, U1.N24 (DEC5)
unnamed: C5.2, C5#2.2, U1.AC5 (DECUSB)
unnamed: C24.2, U1.B24 (XC1), X2.1, X3.1
unnamed: C25.1, U1.A23 (XC2), X3.3
unnamed: C17.1, U1.D2 (XL1/P0.00), X1.2
unnamed: C18.2, U1.F2 (XL2/P0.01), X1.1
unnamed: R3.2, R3#2.2
VBUS: C3.2, C3#2.2, C6.2, C6#2.2, C28.1, U1.AD2 (VBUS), U1.Y2 (VDDH), U4.3 (VI), U5.3 (VI)
VDD_Output: C7.1, C7#2.1, C32.1, C33.1, C34.1, C35.1, C36.1, L1.2, U1.A22 (VDD), U1.AD14 (VDD), U1.AD23 (VDD), U1.B1 (VDD), U1.W1 (VDD)
col_0: S1.2, S15.2, S29.2, S29-1.1, S29-2.1, S43.1, S43-1.2, S43-2.2, S57.1, S57-1.2, S57-2.2, U1.AC9 (P0.14), U2.2 (GPIO0)
col_1: S2.2, S16.2, S30.2, S44.2, S58.1, S58-1.2, S58-2.2, U1.A10 (AIN5/P0.29), U2.3 (GPIO1)
col_2: S3.2, S17.2, S31.2, S45.2, S59.1, S59-1.2, S59-2.2, U1.A8 (AIN7/P0.31), U2.4 (GPIO2)
col_3: S4.2, S18.2, S32.2, S46.2, U1.AD8 (P0.13), U2.5 (GPIO3)
col_4: S5.2, S19.2, S33.2, S47.2, U1.AD10 (P0.15), U2.6 (GPIO4)
col_5: S6.2, S20.2, S34.2, S48.2, U1.AD12 (P0.17), U2.7 (GPIO5)
col_6: S7.2, S21.2, S35.2, S49.2, S60.2, S60-1.1, S60-2.1, U1.AC15 (P0.19), U2.8 (GPIO6)
col_7: S8.2, S22.2, S36.2, S50.2, U1.AD16 (P0.20), U2.9 (GPIO7)
col_8: S9.2, S23.2, S37.2, S51.2, U1.AC17 (P0.21)
col_9: S10.2, S24.2, S38.2, S52.2, U1.AD18 (P0.22)
col_10: S11.2, S25.2, S39.2, S53.2, S61.2, S61-1.2, S61-2.2, U1.AC19 (P0.23)
col_11: S12.2, S26.2, S40.2, S54.2, S62.1, S62-1.2, S62-2.2, U1.AD20 (P0.24)
col_12: S13.2, S27.2, S41.2, S41-1.2, S41-2.2, S55.1, S55-1.2, S55-2.2, S63.1, U1.AC21 (P0.25)
col_13: S14.2, S14-1.2, S14-2.2, S28.2, S28-1.1, S28-2.1, S42.1, S56.2, S64.1, S64-1.2, S64-2.2, U1.AD22 (TRACEDATA0/P1.00)
row_0: D2.1 (K), D3.1 (K), D4.1 (K), D5.1 (K), D6.1 (K), D7.1 (K), D8.1 (K), D9.1 (K), D10.1 (K), D11.1 (K), D12.1 (K), D13.1 (K), D14.1 (K), D15.1 (K), U1.U1 (TRACEDATA1/P0.12)
row_1: D16.1 (K), D17.1 (K), D18.1 (K), D19.1 (K), D20.1 (K), D21.1 (K), D22.1 (K), D23.1 (K), D24.1 (K), D25.1 (K), D26.1 (K), D27.1 (K), D28.1 (K), D29.1 (K), U1.R1 (TRACEDATA3/P1.09)
row_2: D30.1 (K), D31.1 (K), D32.1 (K), D33.1 (K), D34.1 (K), D35.1 (K), D36.1 (K), D37.1 (K), D38.1 (K), D39.1 (K), D40.1 (K), D41.1 (K), D42.1 (K), D43.1 (K), U1.N1 (P0.08)
row_3: D44.1 (K), D45.1 (K), D46.1 (K), D47.1 (K), D48.1 (K), D49.1 (K), D50.1 (K), D51.1 (K), D52.1 (K), D53.1 (K), D54.1 (K), D55.1 (K), D56.1 (K), D57.1 (K), U1.L1 (P0.06)
row_4: D58.1 (K), D59.1 (K), D60.1 (K), D61.1 (K), D62.1 (K), D63.1 (K), D64.1 (K), D65.1 (K), U1.A12 (AIN0/P0.02)
